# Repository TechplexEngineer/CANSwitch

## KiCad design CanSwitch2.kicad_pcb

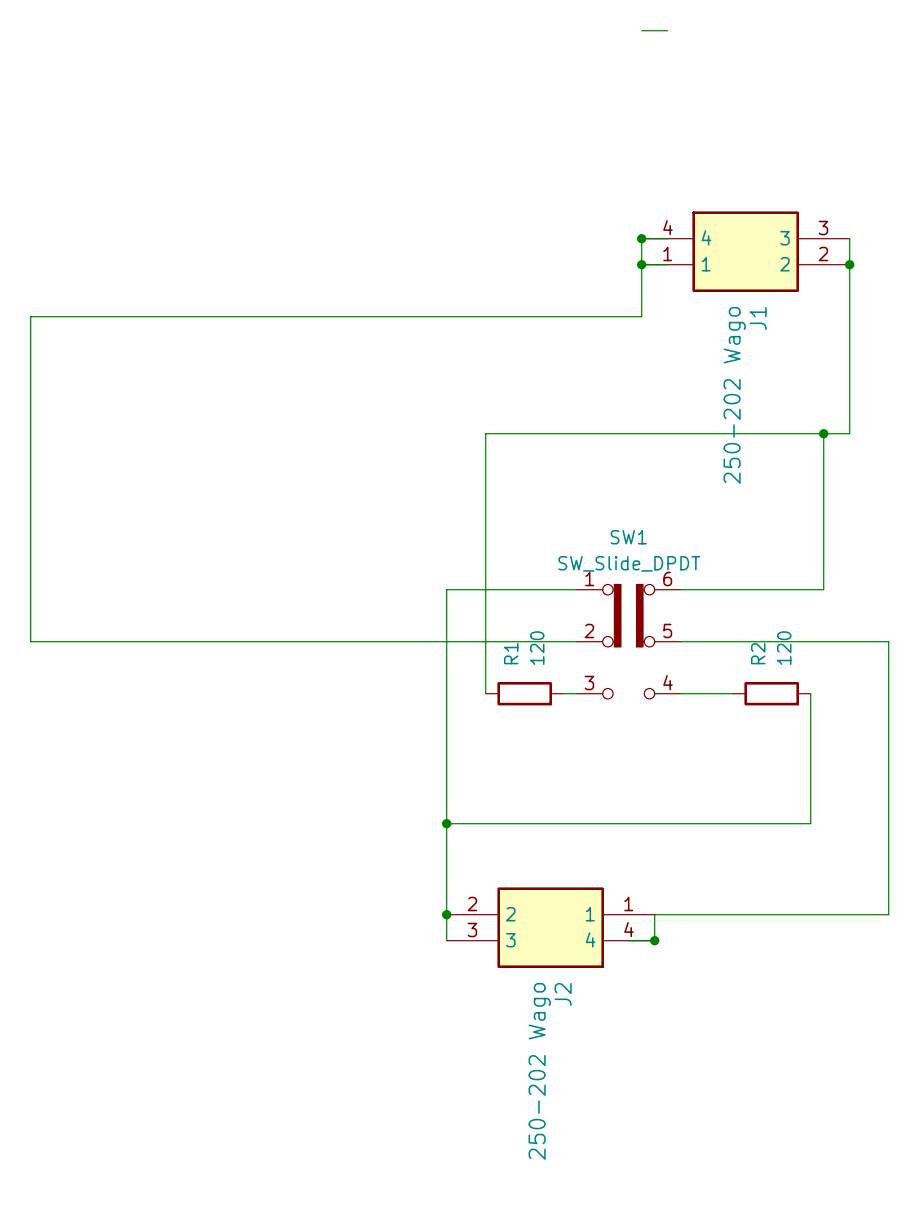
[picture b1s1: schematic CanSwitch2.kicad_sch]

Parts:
J1, J2: 250-202 Wago; 1825960000; Manufacturer_Part_Number 1825960000; Mouser Part Number 470-1825960000
R1, R2: 120; R_0805_2012Metric
SW1: SW_Slide_DPDT; SW_JS202011SCQN

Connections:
unnamed: J1.1, J1.4, SW1.2 (B)
unnamed: J1.2, J1.3, R1.1, SW1.6 (C)
unnamed: J2.1, J2.4, SW1.5 (B)
unnamed: J2.2, J2.3, R2.2, SW1.1 (A)
unnamed: R1.2, SW1.3 (C)
unnamed: R2.1, SW1.4 (A)

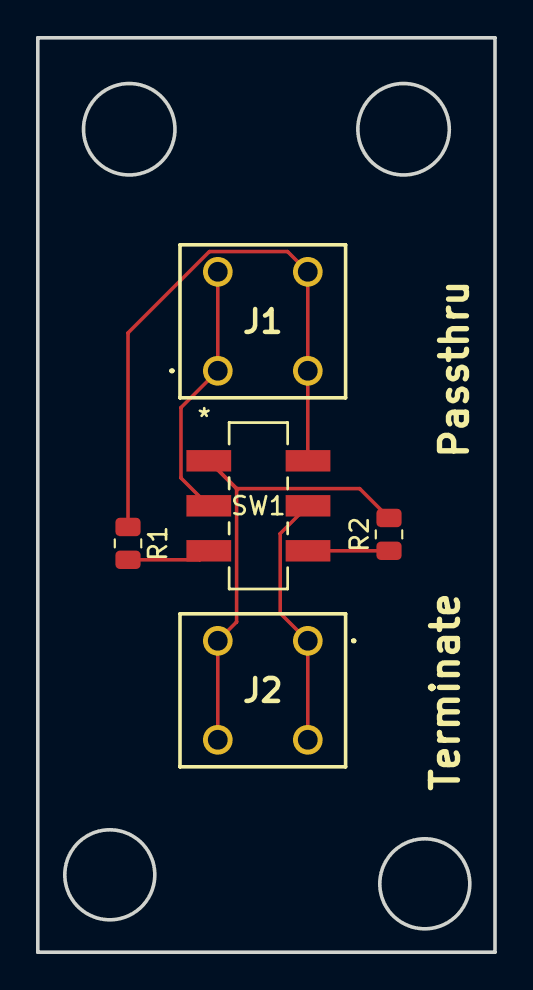
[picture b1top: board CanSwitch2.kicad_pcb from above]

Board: 2 copper layers, 25.4 x 50.8 mm, 5 parts (0 on the bottom side), 6 nets.

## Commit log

2024-11-21 V1 Canswitch
2024-11-21 CJ's Update
